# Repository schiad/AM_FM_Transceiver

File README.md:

# AM_FM8Transceiver
A simple AM and FM Transceiver

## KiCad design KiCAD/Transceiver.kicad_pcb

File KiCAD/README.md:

# AM_FM_Transceiver
A simple AM and FM Transceiver

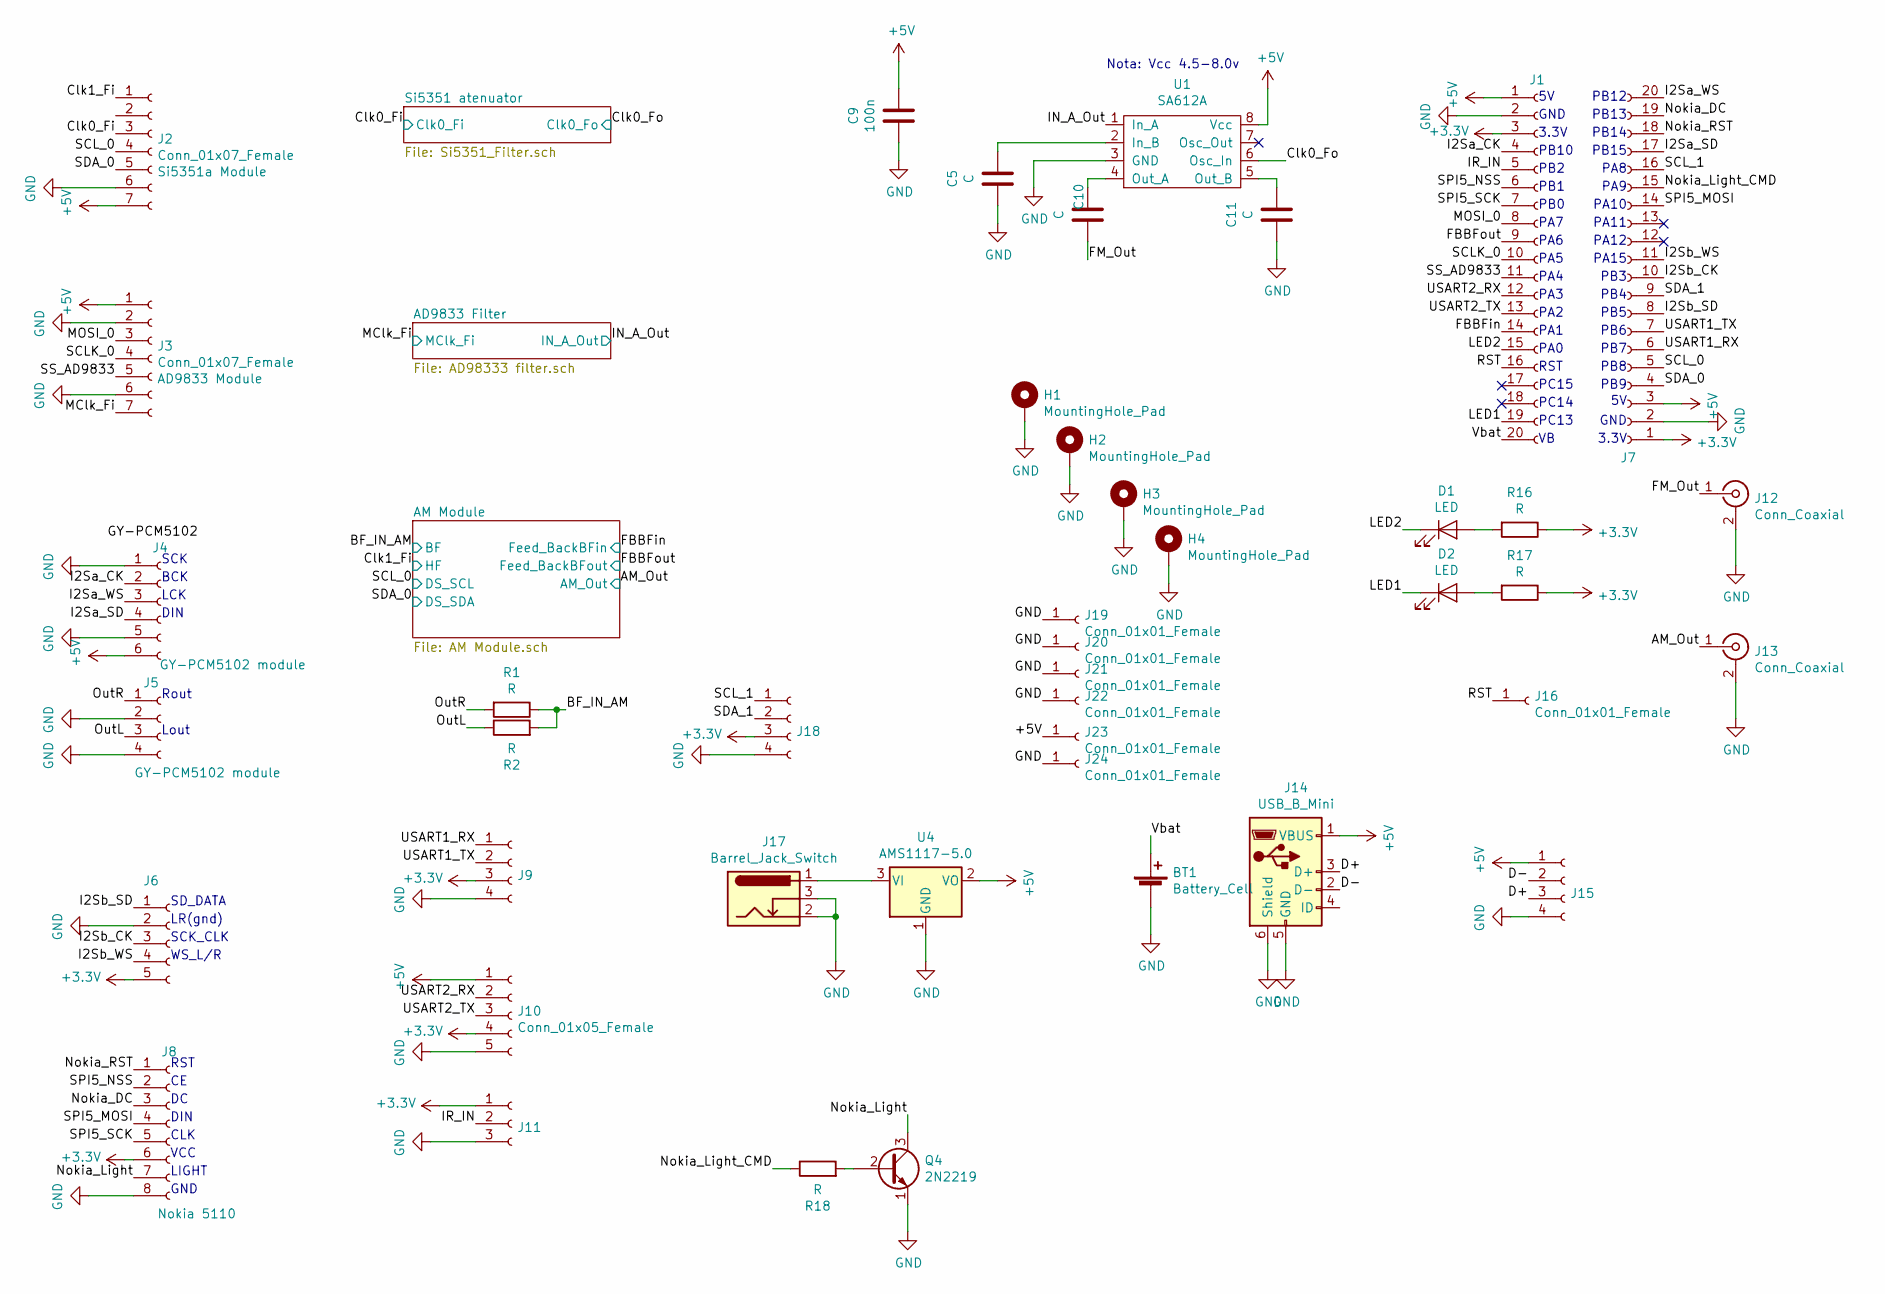
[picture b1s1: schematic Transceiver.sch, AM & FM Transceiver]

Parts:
BT1: Battery_Cell; BatteryHolder_Keystone_103_1x20mm
C5, C10, C11: C; C_0805_2012Metric
C9: 100n; C_0805_2012Metric
D1, D2: LED; LED_0603_1608Metric_Castellated
H1, H2, H3, H4: MountingHole_Pad; MountingHole_2.7mm_M2.5_Pad_Via
J1, J7: Conn_01x20_Female; PinSocket_1x20_P2.54mm_Vertical
J2, J3: Conn_01x07_Female; PinSocket_1x07_P2.54mm_Vertical
J4: Conn_01x06_Female; PinHeader_1x06_P2.54mm_Vertical
J5, J9, J15, J18: Conn_01x04_Female; PinHeader_1x04_P2.54mm_Vertical
J6, J10: Conn_01x05_Female; PinHeader_1x05_P2.54mm_Vertical
J8: Conn_01x08_Female; PinHeader_1x08_P2.54mm_Vertical
J11: Conn_01x03_Female; PinHeader_1x03_P2.54mm_Vertical
J12, J13: Conn_Coaxial; SMA_Amphenol_132289_EdgeMount
J14: USB_B_Mini; USB_Mini-B_Lumberg_2486_01_Horizontal
J16, J19, J20, J21, J22, J23, J24: Conn_01x01_Female; PinHeader_1x01_P2.54mm_Vertical
J17: Barrel_Jack_Switch; BarrelJack_Horizontal
Q4: 2N2219; TO-92L_Inline_Wide
R1, R2, R16, R17, R18: R; R_0805_2012Metric
U1: SA612A; SOIC-8-1EP_3.9x4.9mm_P1.27mm_EP2.29x3mm
U4: AMS1117-5.0; SOT-223-3_TabPin2

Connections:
+3V3: J1.3, J6.5, J7.1, J8.6, J9.3, J10.4, J11.1, J18.3, R16.1, R17.1
+5V: C9.1, J1.1, J2.7, J3.1, J4.6, J7.3, J10.1, J14.1 (VBUS), J15.1, J23.1, U1.8 (Vcc), U4.2 (VO); also elsewhere on the board
/AM_Out: J13.1 (In); also elsewhere on the board
/BF_IN_AM: R1.1, R2.2; also elsewhere on the board
/Clk0_Fi: J2.3; also elsewhere on the board
/Clk0_Fo: U1.6 (Osc_In); also elsewhere on the board
/Clk1_Fi: J2.1; also elsewhere on the board
/D+: J14.3 (D+), J15.3
/D-: J14.2 (D-), J15.2
/FBBFin: J1.14; also elsewhere on the board
/FBBFout: J1.9; also elsewhere on the board
/FM_Out: C10.2, J12.1 (In)
/I2Sa_CK: J1.4, J4.2
/I2Sa_SD: J4.4, J7.17
/I2Sa_WS: J4.3, J7.20
/I2Sb_CK: J6.3, J7.10
/I2Sb_SD: J6.1, J7.8
/I2Sb_WS: J6.4, J7.11
/IN_A_Out: U1.1 (In_A); also elsewhere on the board
/IR_IN: J1.5, J11.2
/LED1: D2.1 (K), J1.19
/LED2: D1.1 (K), J1.15
/MClk_Fi: J3.7; also elsewhere on the board
/MOSI_0: J1.8, J3.3
/Nokia_DC: J7.19, J8.3
/Nokia_Light: J8.7, Q4.3 (C)
/Nokia_Light_CMD: J7.15, R18.1
/Nokia_RST: J7.18, J8.1
/OutL: J5.3, R2.1
/OutR: J5.1, R1.2
/RST: J1.16, J16.1
/SCLK_0: J1.10, J3.4
/SCL_0: J2.4, J7.5; also elsewhere on the board
/SCL_1: J7.16, J18.1
/SDA_0: J2.5, J7.4; also elsewhere on the board
/SDA_1: J7.9, J18.2
/SPI5_MOSI: J7.14, J8.4
/SPI5_NSS: J1.6, J8.2
/SPI5_SCK: J1.7, J8.5
/SS_AD9833: J1.11, J3.5
/USART1_RX: J7.6, J9.1
/USART1_TX: J7.7, J9.2
/USART2_RX: J1.12, J10.2
/USART2_TX: J1.13, J10.3
/Vbat: BT1.1 (+), J1.20
GND: BT1.2 (-), C5.2, C9.2, C11.2, H1.1, H2.1, H3.1, H4.1, J1.2, J2.6, J3.2, J3.6, J4.1, J4.5, J5.2, J5.4, J6.2, J7.2, J8.8, J9.4, J10.5, J11.3, J12.2 (Ext), J13.2 (Ext), J14.5 (GND), J14.6 (Shield), J15.4, J17.2, J17.3, J18.4, J19.1, J20.1, J21.1, J22.1, J24.1, Q4.1 (E), U1.3 (GND), U4.1 (GND); also elsewhere on the board
unnamed: C5.1, U1.2 (In_B)
unnamed: C10.1, U1.4 (Out_A)
unnamed: C11.1, U1.5 (Out_B)
unnamed: D1.2 (A), R16.2
unnamed: D2.2 (A), R17.2
unnamed: J17.1, U4.3 (VI)
unnamed: Q4.2 (B), R18.2

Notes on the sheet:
Nota: Vcc 4.5-8.0v
GND
3.3V
PB10
PB2
PB1
PB0
PA7
PA6
PA5
PA4
PA3
PA2
PA1
PA0
RST
PC15
PC14
PC13
PB9
PB8
PB7
PB6
PB5
PB4
PB3
PA15
PA12
PA11
PA10
PA9
PA8
PB15
PB14
PB13
PB12
SD_DATA
LR(gnd)
WS_L/R
SCK_CLK

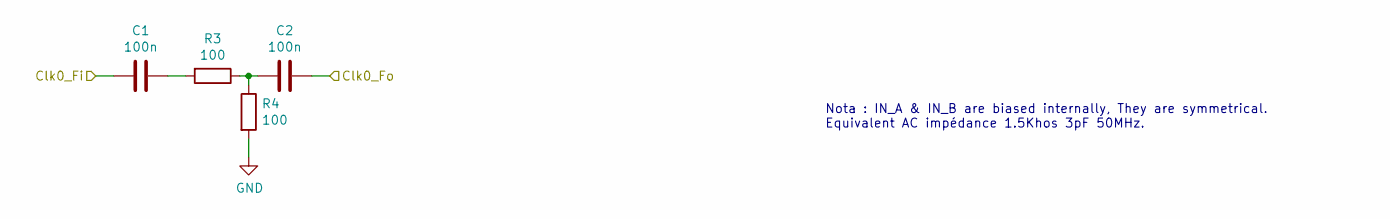
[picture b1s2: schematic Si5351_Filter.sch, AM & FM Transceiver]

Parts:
C1, C2: 100n; C_0805_2012Metric
R3, R4: 100; R_0805_2012Metric

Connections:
/Clk0_Fi: C1.2; also elsewhere on the board
/Clk0_Fo: C2.1; also elsewhere on the board
GND: R4.2; also elsewhere on the board
unnamed: C1.1, R3.2
unnamed: C2.2, R3.1, R4.1

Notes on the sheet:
Nota : IN_A & IN_B are biased internally, They are symmetrical. Equivalent AC impédance 1.5Khos 3pF 50MHz.

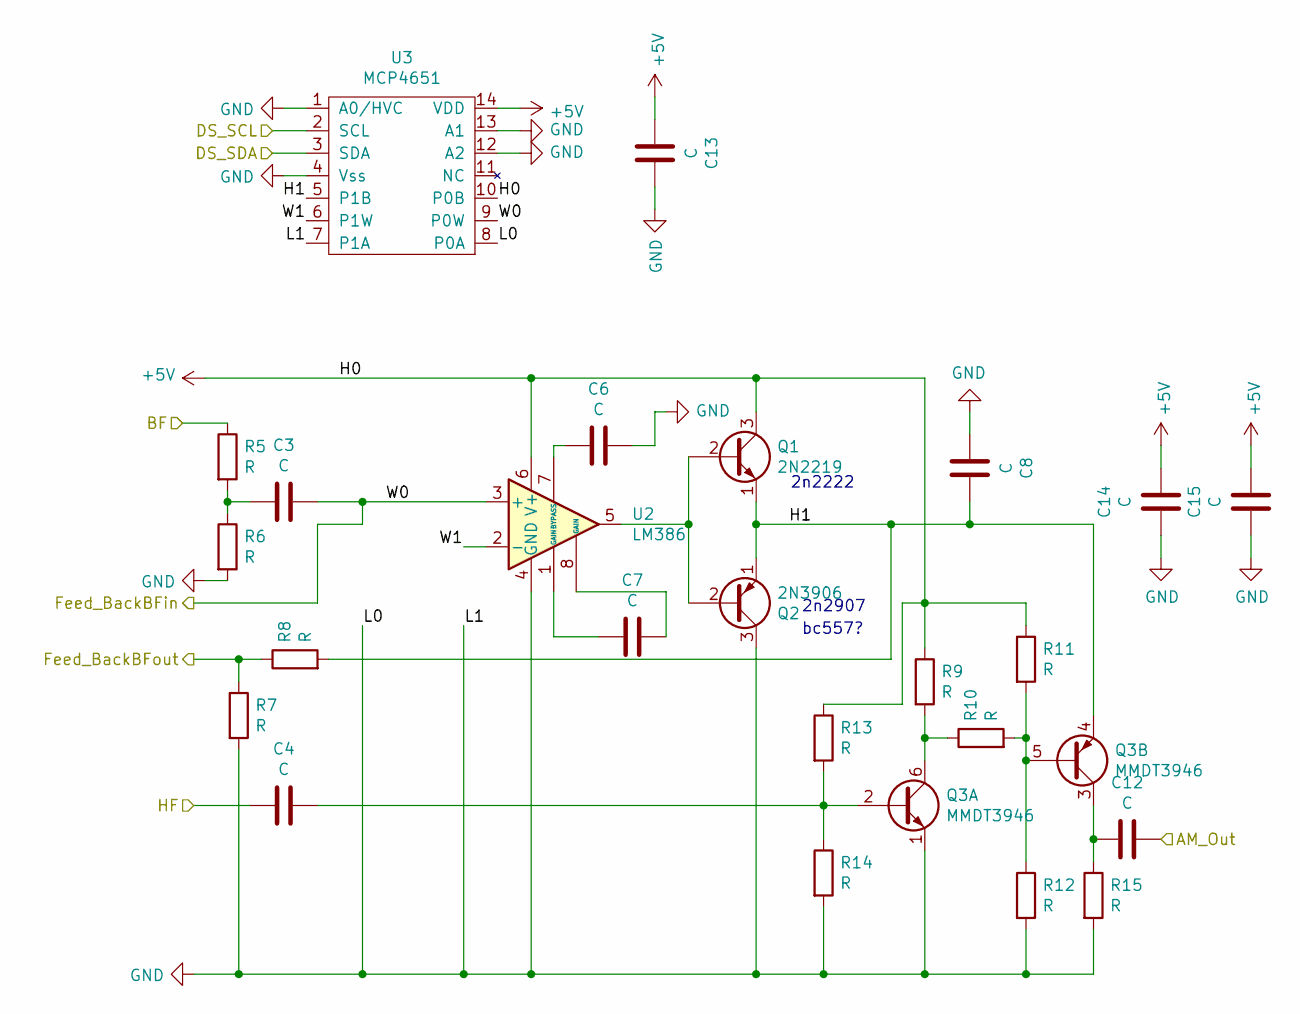
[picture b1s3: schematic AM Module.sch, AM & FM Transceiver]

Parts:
C3, C4, C6, C7, C8, C12, C13, C14, C15: C; C_0805_2012Metric
Q1: 2N2219; TO-92L_Inline_Wide
Q2: 2N3906; TO-92_Inline_Wide
Q3: MMDT3946; SOT-363_SC-70-6
R5, R6, R7, R8, R9, R10, R11, R12, R13, R14, R15: R; R_0805_2012Metric
U2: LM386; DIP-8_W7.62mm
U3: MCP4651; TSSOP-14_4.4x5mm_P0.65mm

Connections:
+5V: C13.2, C14.1, C15.1, Q1.3 (C), R9.1, R11.1, R13.1, U2.6 (V+), U3.10 (P0B), U3.14 (VDD); also elsewhere on the board
/AM Module/H1: C8.1, Q1.1 (E), Q2.1 (E), Q3.4 (E2), R8.2, U3.5 (P1B)
/AM Module/W1: U2.2 (-), U3.6 (P1W)
/AM_Out: C12.1; also elsewhere on the board
/BF_IN_AM: R5.1; also elsewhere on the board
/Clk1_Fi: C4.2; also elsewhere on the board
/FBBFin: C3.1, U2.3 (+), U3.9 (P0W); also elsewhere on the board
/FBBFout: R7.1, R8.1; also elsewhere on the board
/SCL_0: U3.2 (SCL); also elsewhere on the board
/SDA_0: U3.3 (SDA); also elsewhere on the board
GND: C6.1, C8.2, C13.1, C14.2, C15.2, Q2.3 (C), Q3.1 (E1), R6.2, R7.2, R12.2, R14.2, R15.2, U2.4 (GND), U3.1 (A0/HVC), U3.4 (Vss), U3.7 (P1A), U3.8 (P0A), U3.12 (A2), U3.13 (A1); also elsewhere on the board
unnamed: C3.2, R5.2, R6.1
unnamed: C4.1, Q3.2 (B1), R13.2, R14.1
unnamed: C6.2, U2.7 (BYPASS)
unnamed: C7.1, U2.8 (GAIN)
unnamed: C7.2, U2.1 (GAIN)
unnamed: C12.2, Q3.3 (C2), R15.1
unnamed: Q1.2 (B), Q2.2 (B), U2.5
unnamed: Q3.5 (B2), R10.2, R11.2, R12.1
unnamed: Q3.6 (C1), R9.2, R10.1

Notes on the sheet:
2n2222
2n2907
bc557?

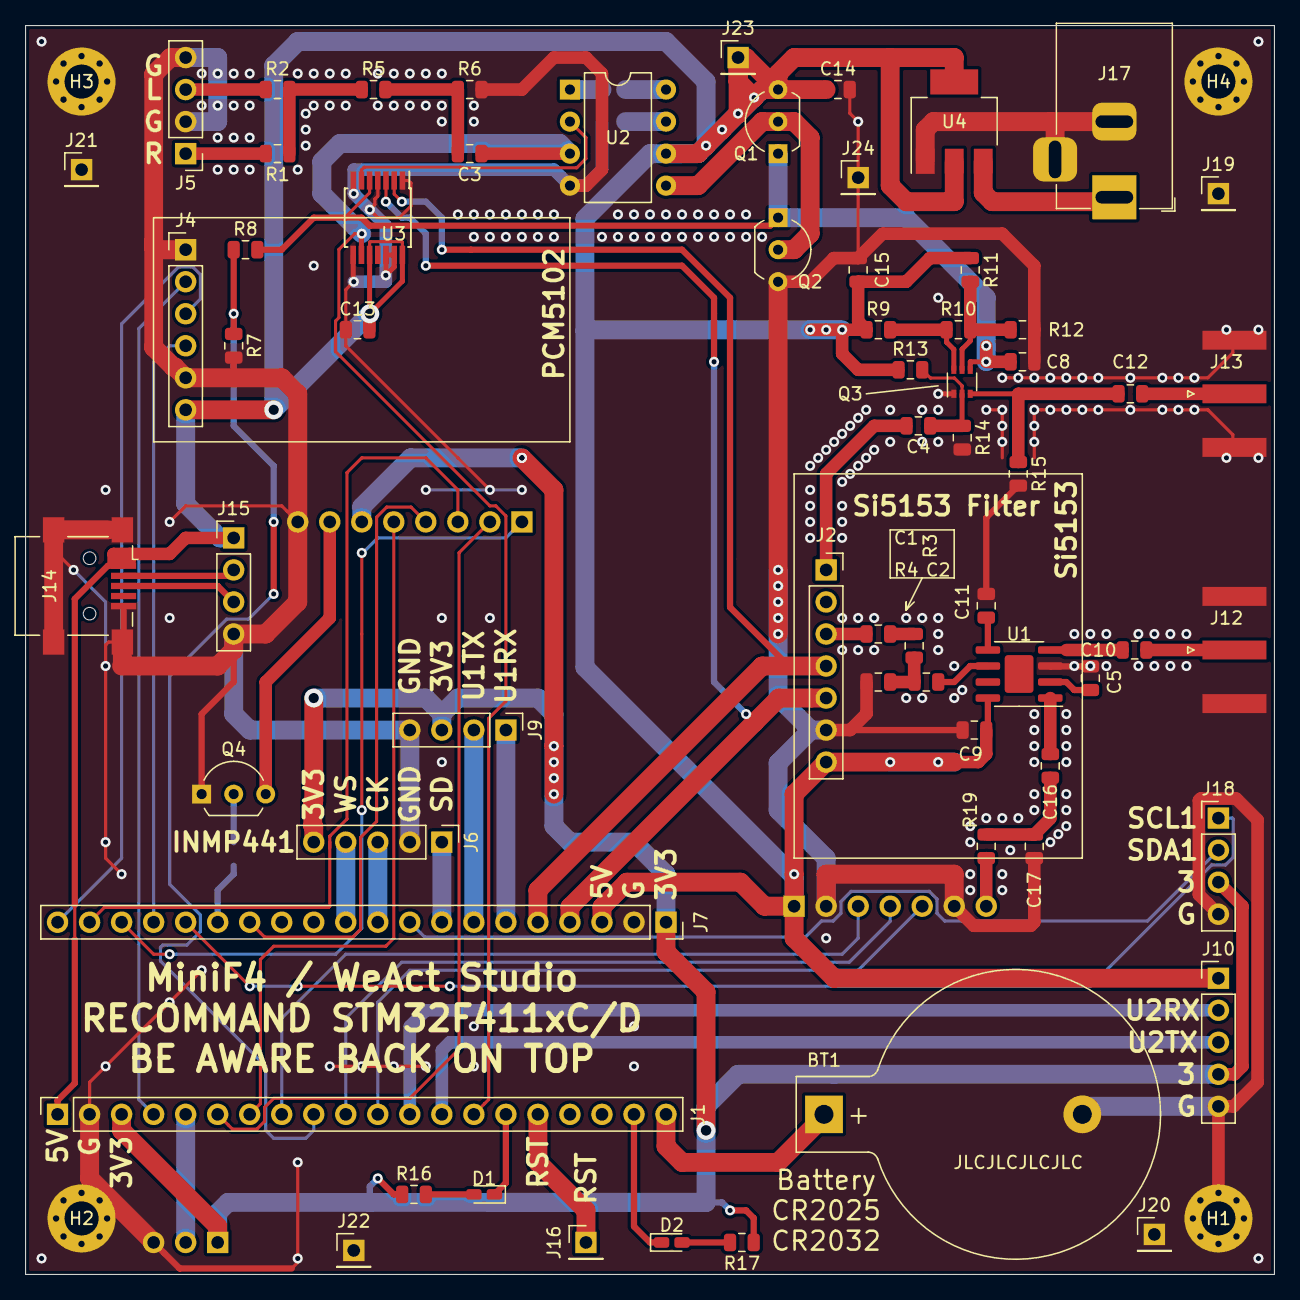
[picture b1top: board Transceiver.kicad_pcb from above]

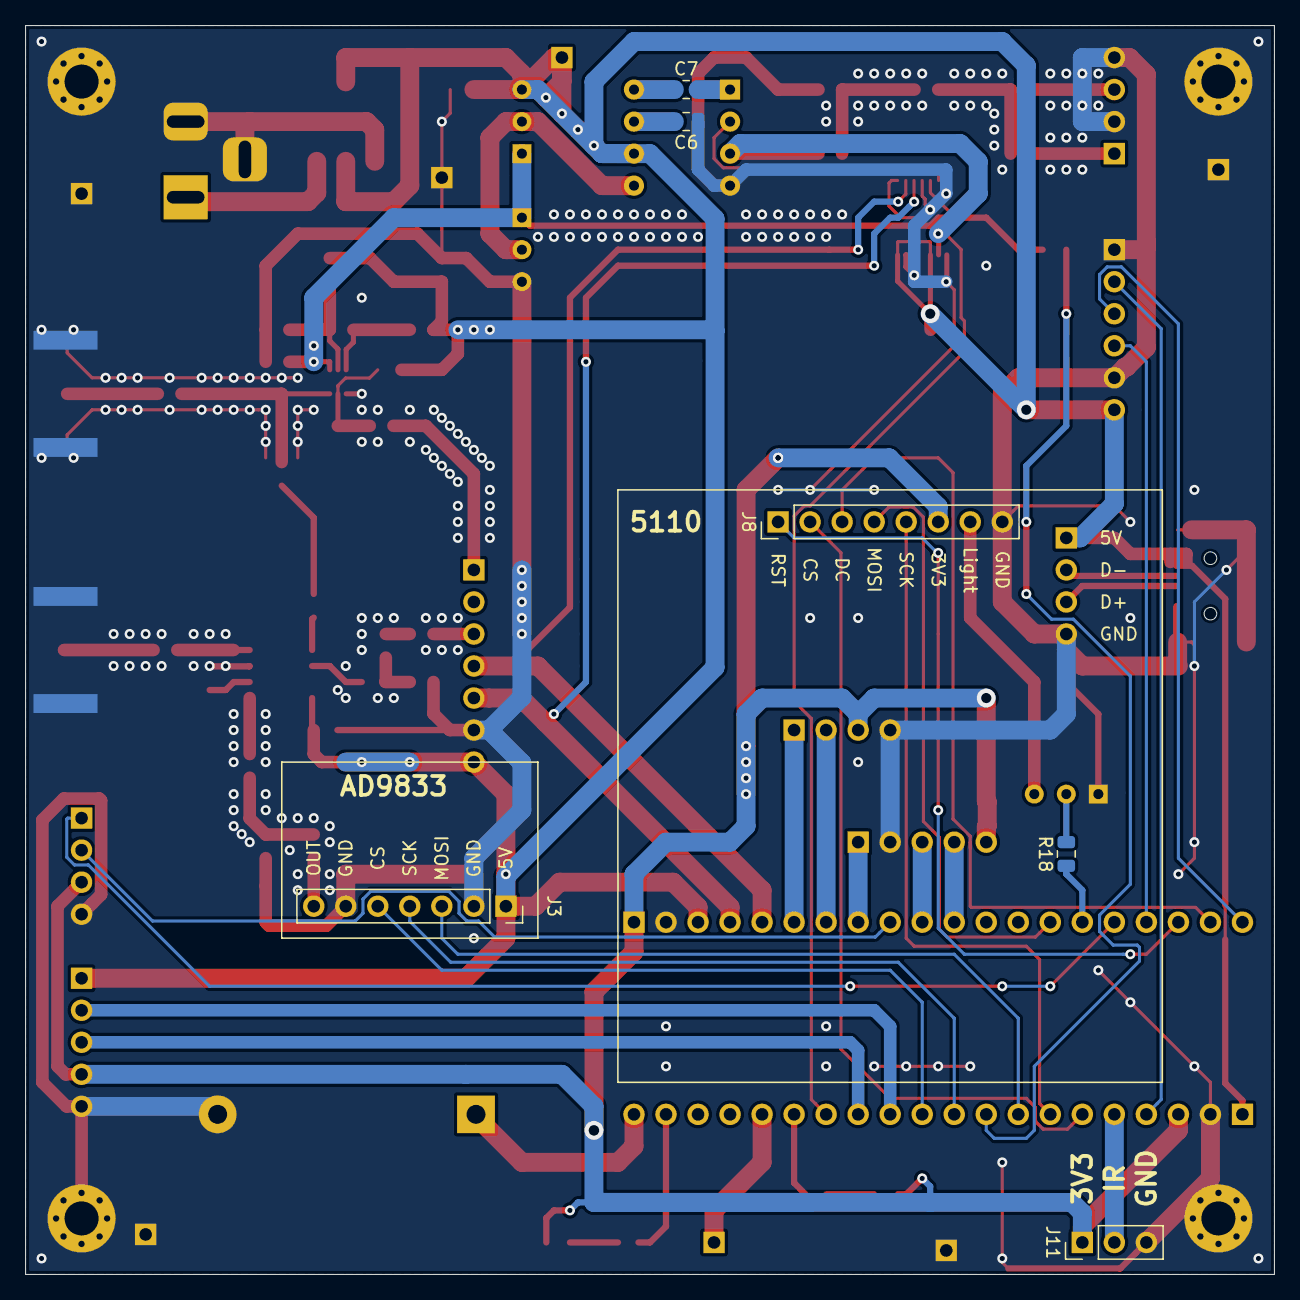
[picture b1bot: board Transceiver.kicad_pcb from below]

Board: 2 copper layers, 99.1 x 99.1 mm, 75 parts (6 on the bottom side), 67 nets.

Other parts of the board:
C16, C17: 100n; C_0805_2012Metric
R19: R; R_0805_2012Metric

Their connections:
/IN_A_Out: C16.2; also elsewhere on the board
/MClk_Fi: R19.1; also elsewhere on the board
GND: C17.1; also elsewhere on the board
unnamed: C16.1, C17.2, R19.2

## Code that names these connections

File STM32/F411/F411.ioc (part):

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Mcu.Name=STM32F411C(C-E)Ux
Mcu.Package=UFQFPN48
Mcu.UserName=STM32F411CCUx
PA0-WKUP.GPIOParameters=GPIO_Label
PA0-WKUP.GPIO_Label=LED2
PA0-WKUP.Signal=GPIO_Output
PA1.GPIOParameters=GPIO_Label
PA1.GPIO_Label=FBBFin
PA1.Signal=ADCx_IN1
PA10.Mode=TX_Only_Simplex_Unidirect_Master
PA10.Signal=SPI5_MOSI
PA11.Mode=Device_Only
PA11.Signal=USB_OTG_FS_DM
PA12.Mode=Device_Only
PA12.Signal=USB_OTG_FS_DP
PA13.Mode=Serial_Wire
PA13.Signal=SYS_JTMS-SWDIO
PA14.Mode=Serial_Wire
PA14.Signal=SYS_JTCK-SWCLK
PA15.Mode=Half_Duplex_Master
PA15.Signal=I2S3_WS
PA2.Mode=Asynchronous
PA2.Signal=USART2_TX
PA3.Mode=Asynchronous
PA3.Signal=USART2_RX
PA4.GPIOParameters=GPIO_Label
PA4.GPIO_Label=AD9833_CS
PA4.Signal=GPIO_Output
PA5.Mode=TX_Only_Simplex_Unidirect_Master
PA5.Signal=SPI1_SCK
PA6.GPIOParameters=GPIO_Label
PA6.GPIO_Label=FBBFout
PA6.Signal=ADCx_IN6
PA7.Mode=TX_Only_Simplex_Unidirect_Master
PA7.Signal=SPI1_MOSI
PA8.Mode=I2C
PA8.Signal=I2C3_SCL
PA9.GPIOParameters=GPIO_ModeDefaultPP,GPIO_Speed,GPIO_PuPd,GPIO_Label
PA9.GPIO_Label=Nokia_Light
PA9.GPIO_ModeDefaultPP=GPIO_MODE_AF_PP
PA9.GPIO_PuPd=GPIO_PULLDOWN
PA9.GPIO_Speed=GPIO_SPEED_FREQ_VERY_HIGH
PA9.Signal=S_TIM1_CH2
PB0.Mode=TX_Only_Simplex_Unidirect_Master
PB0.Signal=SPI5_SCK
PB1.GPIOParameters=GPIO_Label
PB1.GPIO_Label=Nokia_CE
PB1.Signal=GPIO_Output
PB10.Mode=Half_Duplex_Master
PB10.Signal=I2S2_CK
PB12.Mode=Half_Duplex_Master
PB12.Signal=I2S2_WS
PB13.GPIOParameters=GPIO_Label
PB13.GPIO_Label=Nokia_DC
PB13.Signal=GPIO_Output
PB14.GPIOParameters=GPIO_Label
PB14.GPIO_Label=Nokia_RST
PB14.Signal=GPIO_Output
PB15.Mode=Half_Duplex_Master
PB15.Signal=I2S2_SD
PB2.GPIOParameters=GPIO_PuPd,GPIO_Label,GPIO_ModeDefaultEXTI
PB2.GPIO_Label=IR_IN
PB2.GPIO_ModeDefaultEXTI=GPIO_MODE_IT_RISING_FALLING
PB2.GPIO_PuPd=GPIO_PULLUP
PB2.Signal=GPXTI2
PB3.Mode=Half_Duplex_Master
PB3.Signal=I2S3_CK
PB4.Mode=I2C
PB4.Signal=I2C3_SDA
PB5.Mode=Half_Duplex_Master
PB5.Signal=I2S3_SD
PB6.Mode=Asynchronous
PB6.Signal=USART1_TX
PB7.Mode=Asynchronous
PB7.Signal=USART1_RX
PB8.Mode=I2C
PB8.Signal=I2C1_SCL
PB9.Mode=I2C
PB9.Signal=I2C1_SDA
PC13-ANTI_TAMP.GPIOParameters=GPIO_Label
PC13-ANTI_TAMP.GPIO_Label=LED1
PC13-ANTI_TAMP.Signal=GPIO_Output
PC14-OSC32_IN.Mode=LSE-External-Oscillator
PC14-OSC32_IN.Signal=RCC_OSC32_IN
PC15-OSC32_OUT.Mode=LSE-External-Oscillator
PC15-OSC32_OUT.Signal=RCC_OSC32_OUT
PH0\ -\ OSC_IN.Mode=HSE-External-Oscillator
PH0\ -\ OSC_IN.Signal=RCC_OSC_IN
PH1\ -\ OSC_OUT.Mode=HSE-External-Oscillator
PH1\ -\ OSC_OUT.Signal=RCC_OSC_OUT
RCC.HSE_VALUE=25000000
RCC.SYSCLKFreq_VALUE=96000000
RCC.SYSCLKSource=RCC_SYSCLKSOURCE_PLLCLK
board=custom

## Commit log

2020-03-17 Update READ ME
2020-03-22 First Commit, KiCAD global ok
2020-03-24 Add voltage divider for PCM5102A output, sort files in folder by softwares
2020-03-27 Add mcu
2020-04-02 Add MCU module and other modules
2020-04-03 Just save files Begin PCB
2020-04-06 Make PCB and change NPN and PNP for AM output
2020-04-17 Schematics and PCB update
2020-06-07 Product version 1
2020-09-14 Version ok Si5351 + AD9833 + IR for control SI and AD
2021-01-15 push
